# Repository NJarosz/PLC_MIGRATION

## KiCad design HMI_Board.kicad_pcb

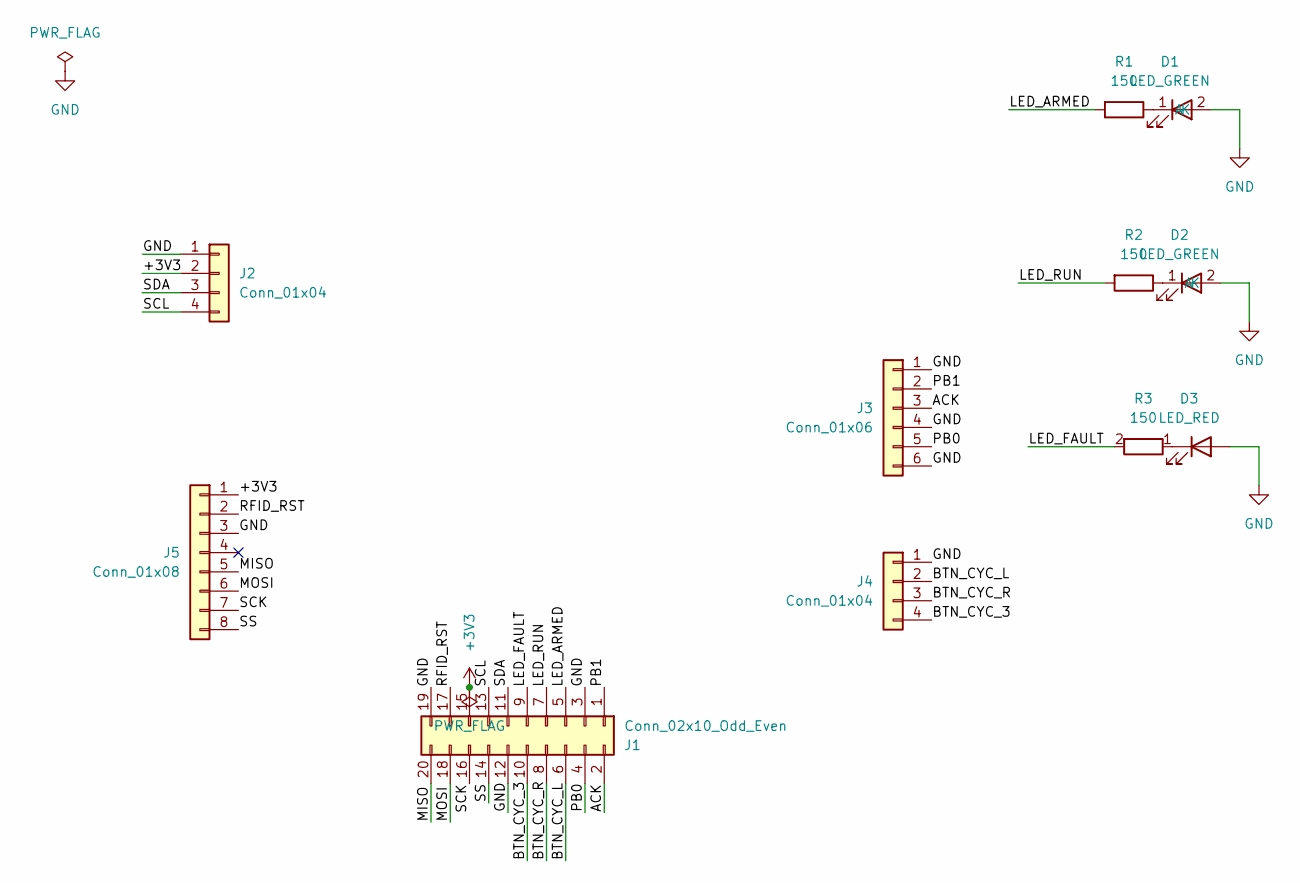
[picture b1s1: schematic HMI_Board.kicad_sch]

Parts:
D1, D2: LED_GREEN; LED_D3.0mm
D3: LED_RED; LED_D3.0mm
J1: Conn_02x10_Odd_Even; IDC-Header_2x10_P2.54mm_Latch_Horizontal
J2, J4: Conn_01x04; PinHeader_1x04_P2.54mm_Horizontal
J3: Conn_01x06; PinHeader_1x06_P2.54mm_Horizontal
J5: Conn_01x08; PinHeader_1x08_P2.54mm_Horizontal
R1, R2, R3: 150; R_Axial_DIN0207_L6.3mm_D2.5mm_P10.16mm_Horizontal

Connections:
+3V3: J1.15, J2.2, J5.1
/ACK: J1.2, J3.3
/BTN_CYC_3: J1.10, J4.4
/BTN_CYC_L: J1.6, J4.2
/BTN_CYC_R: J1.8, J4.3
/LED_ARMED: J1.5, R1.2
/LED_FAULT: J1.9, R3.2
/LED_RUN: J1.7, R2.2
/MISO: J1.20, J5.5
/MOSI: J1.18, J5.6
/PB0: J1.4, J3.5
/PB1: J1.1, J3.2
/RFID_RST: J1.17, J5.2
/SCK: J1.16, J5.7
/SCL: J1.13, J2.4
/SDA: J1.11, J2.3
/SS: J1.14, J5.8
GND: D1.2 (A), D2.2 (A), D3.2 (A), J1.3, J1.12, J1.19, J2.1, J3.1, J3.4, J3.6, J4.1, J5.3
unnamed: D1.1 (K), R1.1
unnamed: D2.1 (K), R2.1
unnamed: D3.1 (K), R3.1

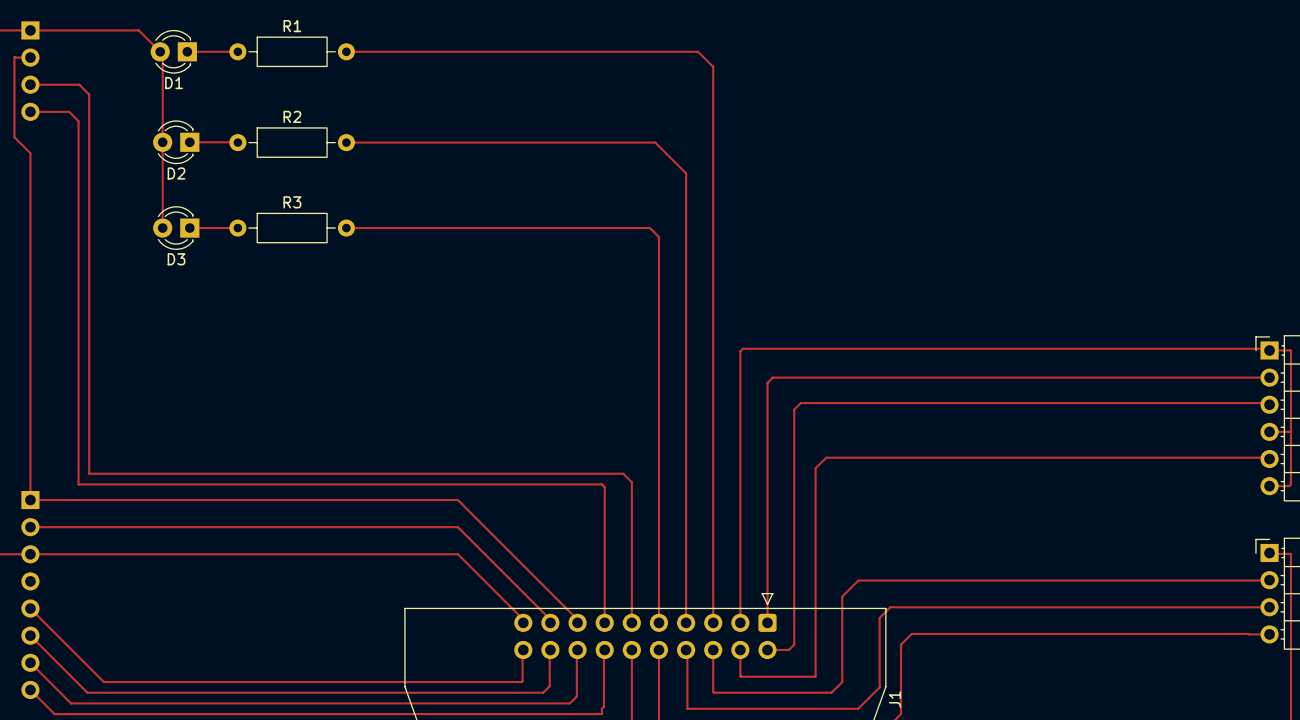
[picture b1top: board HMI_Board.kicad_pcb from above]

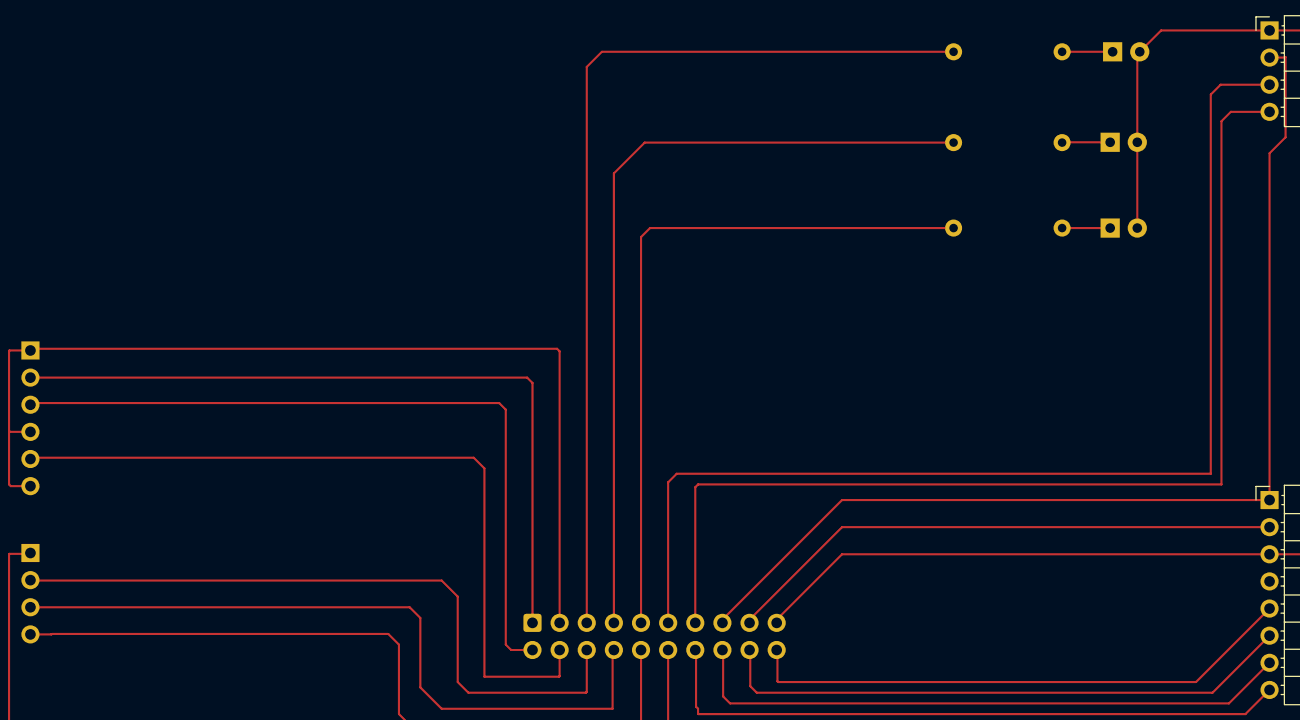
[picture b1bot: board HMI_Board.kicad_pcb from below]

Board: 2 copper layers, 11 parts (2 on the bottom side), 21 nets.

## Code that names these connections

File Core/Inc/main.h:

/* USER CODE BEGIN Header */
/**
  ******************************************************************************
  * @file           : main.h
  * @brief          : Header for main.c file.
  *                   This file contains the common defines of the application.
  ******************************************************************************
  * @attention
  *
  * Copyright (c) 2026 STMicroelectronics.
  * All rights reserved.
  *
  * This software is licensed under terms that can be found in the LICENSE file
  * in the root directory of this software component.
  * If no LICENSE file comes with this software, it is provided AS-IS.
  *
  ******************************************************************************
  */
/* USER CODE END Header */

/* Define to prevent recursive inclusion -------------------------------------*/
#ifndef __MAIN_H
#define __MAIN_H

#ifdef __cplusplus
extern "C" {
#endif

/* Includes ------------------------------------------------------------------*/
#include "stm32f4xx_hal.h"

/* Private includes ----------------------------------------------------------*/
/* USER CODE BEGIN Includes */

/* USER CODE END Includes */

/* Exported types ------------------------------------------------------------*/
/* USER CODE BEGIN ET */

/* USER CODE END ET */

/* Exported constants --------------------------------------------------------*/
/* USER CODE BEGIN EC */

/* USER CODE END EC */

/* Exported macro ------------------------------------------------------------*/
/* USER CODE BEGIN EM */

/* USER CODE END EM */

/* Exported functions prototypes ---------------------------------------------*/
void Error_Handler(void);

/* USER CODE BEGIN EFP */

/* USER CODE END EFP */

/* Private defines -----------------------------------------------------------*/
#define B1_Pin GPIO_PIN_13
#define B1_GPIO_Port GPIOC
#define USART_TX_Pin GPIO_PIN_2
#define USART_TX_GPIO_Port GPIOA
#define USART_RX_Pin GPIO_PIN_3
#define USART_RX_GPIO_Port GPIOA
#define LD2_Pin GPIO_PIN_5
#define LD2_GPIO_Port GPIOA
#define RFID_CS_Pin GPIO_PIN_12
#define RFID_CS_GPIO_Port GPIOB
#define RFID_RST_Pin GPIO_PIN_8
#define RFID_RST_GPIO_Port GPIOC
#define TMS_Pin GPIO_PIN_13
#define TMS_GPIO_Port GPIOA
#define TCK_Pin GPIO_PIN_14
#define TCK_GPIO_Port GPIOA
#define SWO_Pin GPIO_PIN_3
#define SWO_GPIO_Port GPIOB

/* USER CODE BEGIN Private defines */

// ── Relay outputs — all on GPIOA, active-high into ULN2803A ──────────────
// PA0-PA1: relays 1-2; PA4-PA8: relays 3-7 (PA2/PA3=UART, PA9/PA10=UART1);
// PA11: relay 8. On Nucleo bench: PA5 also drives LD2 (green LED) — useful
// as a visual indicator for relay 4 during testing.
#define RELAY1_Pin GPIO_PIN_0
#define RELAY1_Port GPIOA

#define RELAY2_Pin GPIO_PIN_1
#define RELAY2_Port GPIOA

#define RELAY3_Pin GPIO_PIN_4
#define RELAY3_Port GPIOA

#define RELAY4_Pin GPIO_PIN_5
#define RELAY4_Port GPIOA

#define RELAY5_Pin GPIO_PIN_6
#define RELAY5_Port GPIOA

#define RELAY6_Pin GPIO_PIN_7
#define RELAY6_Port GPIOA

#define RELAY7_Pin GPIO_PIN_8
#define RELAY7_Port GPIOA

#define RELAY8_Pin GPIO_PIN_11
#define RELAY8_Port GPIOA

#define NUM_RELAYS 8

// ── Panel button inputs — active-low, pull-up (GPIOB) ────────────────────
#define RUN_Pin          GPIO_PIN_0
#define RUN_Port         GPIOB
#define FETCH_Pin        GPIO_PIN_1
#define FETCH_Port       GPIOB
#define ACK_BTN_Pin      GPIO_PIN_10
#define ACK_BTN_GPIO_Port GPIOB

#define ESTOP_Pin        GPIO_PIN_4
#define ESTOP_Port       GPIOB

// ── External cycle-start / hand button inputs — active-low, pull-up ──────
#define BTN_CYC_L_Pin    GPIO_PIN_14
#define BTN_CYC_L_Port   GPIOB
#define BTN_CYC_R_Pin    GPIO_PIN_15
#define BTN_CYC_R_Port   GPIOB
#define BTN_CYC_3_Pin    GPIO_PIN_11
#define BTN_CYC_3_Port   GPIOC

// ── Manual mode switch inputs — active-high, pull-down, PC3-PC10 ─────────
// Consecutive 8-bit block: sw_states = (GPIOC->IDR >> 3) & 0xFF
// Series LED circuit in pendant: 3.3V → switch → GPIO → LED → 220Ω → GND.
#define MAN_SW1_Pin   GPIO_PIN_3
#define MAN_SW1_Port  GPIOC
#define MAN_SW2_Pin   GPIO_PIN_4
#define MAN_SW2_Port  GPIOC
#define MAN_SW3_Pin   GPIO_PIN_5
#define MAN_SW3_Port  GPIOC
#define MAN_SW4_Pin   GPIO_PIN_6
#define MAN_SW4_Port  GPIOC
#define MAN_SW5_Pin   GPIO_PIN_7
#define MAN_SW5_Port  GPIOC
#define MAN_SW6_Pin   GPIO_PIN_8
#define MAN_SW6_Port  GPIOC
#define MAN_SW7_Pin   GPIO_PIN_9
#define MAN_SW7_Port  GPIOC
#define MAN_SW8_Pin   GPIO_PIN_10
#define MAN_SW8_Port  GPIOC

// ── RFID SPI ──────────────────────────────────────────────────────────────
#define RFID_CS_Pin    GPIO_PIN_12
#define RFID_CS_Port   GPIOB
#define RFID_RST_Pin   GPIO_PIN_12
#define RFID_RST_Port  GPIOA

// ── ESP32 UART ────────────────────────────────────────────────────────────
#define ESP_TX_Pin GPIO_PIN_9
#define ESP_TX_GPIO_Port GPIOA
#define ESP_RX_Pin GPIO_PIN_10
#define ESP_RX_GPIO_Port GPIOA

// ── HMI board LED drive outputs — active-high, push-pull (GPIOB) ─────────
#define LED_ARMED_Pin   GPIO_PIN_5
#define LED_ARMED_Port  GPIOB
#define LED_RUN_Pin     GPIO_PIN_7
#define LED_RUN_Port    GPIOB
#define LED_FAULT_Pin   GPIO_PIN_6
#define LED_FAULT_Port  GPIOB

/* USER CODE END Private defines */

#ifdef __cplusplus
}
#endif

#endif /* __MAIN_H */

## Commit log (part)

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2026-04-16 altered pi setup.sh
2026-04-16 updated compiler / sequence format to be more human readable, bypassing bitmask values and using an array of relay values
2026-04-29 updated files for SHA encoding
2026-04-29 updated files for metadata encoding to MCU along with sequence
2026-04-29 updated files for metadata that includes part and machine num
2026-04-29 added functionality for outgoing logs back to the pi
2026-05-01 added heartbeat clock sync and updated logging functions included sequence data in heartbeats
2026-05-01 added deploy.sh and eventcodes.py files
2026-05-07 Added functionality for RFID Scanner
2026-05-07 user UI v1.0
2026-05-07 UI version 1.1- edited for PLC01 instead of devpi01 and fixed the restart service
2026-05-07 updated app.py so that the plc registry wont stay blank after restart
2026-05-07 updated that previous fix, but actually this time
2026-05-07 udpated the file names for the sequences so that there's no clash between sequence name and sequence file name when deploying
2026-05-07 updated UI to separate out part and mach number from sequence. Also updated to remind user to update sequence on plc
2026-05-07 Updated the sequence designer so target PLC is no longer required. Also updated PLC card to add sequence from there
2026-05-07 more UI functionality. fix deploy button on seq screen and card layout
2026-05-07 updated layout on card for disconnected status
2026-05-12 added count and count goal function
2026-05-13 Updated count to be persistent, also added a second user button and adjusted button functionality
2026-05-13 updated UI to add reset count
2026-05-13 updated some LCD code
